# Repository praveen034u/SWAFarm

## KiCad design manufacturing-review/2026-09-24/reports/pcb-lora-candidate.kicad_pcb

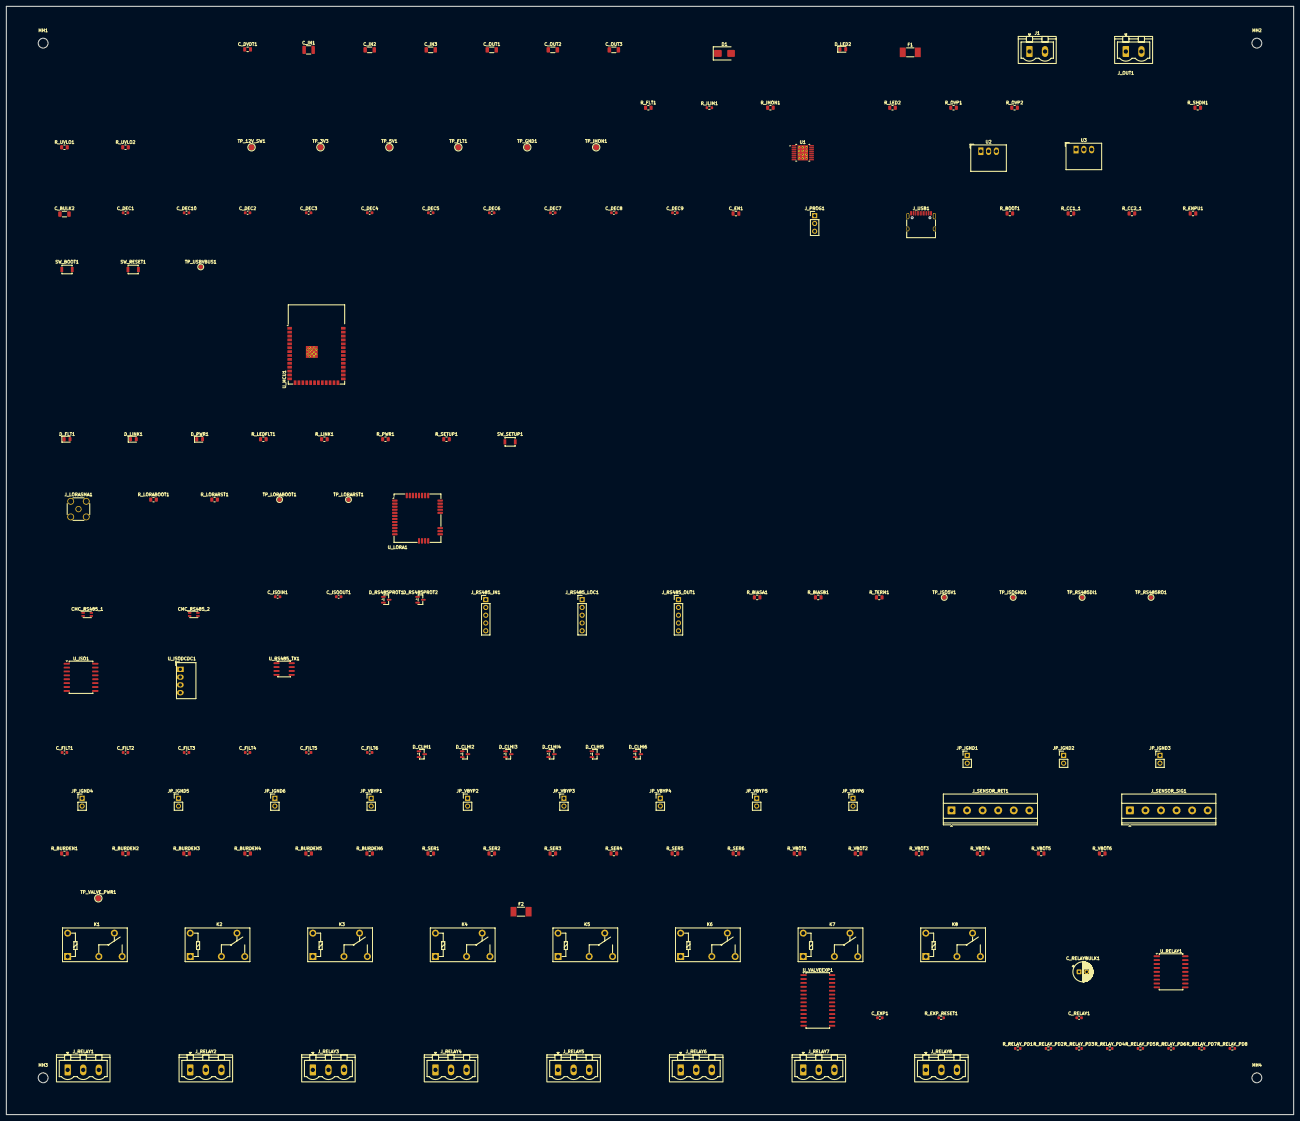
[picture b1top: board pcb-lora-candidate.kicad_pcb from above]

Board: 4 copper layers, 420.0 x 361.6 mm, 165 parts (0 on the bottom side), 114 nets, no tracks yet.

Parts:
CMC_RS485_1, CMC_RS485_2: 744232090; L_CommonMode_Wurth_WE-CNSW-1206
C_BULK2: 10uF; C_1206_3216Metric
C_DEC1, C_DEC2, C_DEC3, C_DEC4, C_DEC5, C_DEC6, C_DEC7, C_DEC8, C_DEC9, C_DEC10: 100nF; C_0603_1608Metric
C_DVDT1: 100nF 50V X7R; C_0805_2012Metric
C_EN1: 1uF; C_0805_2012Metric
C_EXP1: 100nF; C_0603_1608Metric
C_FILT1, C_FILT2, C_FILT3, C_FILT4, C_FILT5, C_FILT6: 100nF; C_0603_1608Metric
C_IN1: 10uF 63V X7R; C_1210_3225Metric
C_IN2, C_IN3: 10uF 25V; C_1206_3216Metric
C_ISOIN1: 100nF; C_0603_1608Metric
C_ISOOUT1: 100nF; C_0603_1608Metric
C_OUT1: 10uF 25V; C_1206_3216Metric
C_OUT2, C_OUT3: 22uF 10V; C_1206_3216Metric
C_RELAY1: 100nF; C_0603_1608Metric
C_RELAYBULK1: 100uF 25V; CP_Radial_D6.3mm_P2.50mm
D1: SMBJ18CA; D_SMB
D_CLHI1, D_CLHI2, D_CLHI3, D_CLHI4, D_CLHI5, D_CLHI6: BAV99; SOT-23
D_FLT1: Red; LED_0805_2012Metric
D_LED2: Green_3V3Present; LED_0805_2012Metric
D_LINK1: Yellow; LED_0805_2012Metric
D_PWR1: Green; LED_0805_2012Metric
D_RS485PROT1, D_RS485PROT2: SM712-02HTG; SOT-23
F1: 2A fast / 125V; Fuse_Littelfuse-NANO2-451_453
F2: 1A fast / 125V; Fuse_Littelfuse-NANO2-451_453
J1: 12V IN: + / GND; PhoenixContact_MSTBVA_2,5_2-G-5,08_1x02_P5.08mm_Vertical
JP_IGND1, JP_IGND2, JP_IGND3, JP_IGND4, JP_IGND5, JP_IGND6: I_mode_gnd; PinHeader_1x02_P2.54mm_Vertical
JP_VBYP1, JP_VBYP2, JP_VBYP3, JP_VBYP4, JP_VBYP5, JP_VBYP6: V_mode_bypass; PinHeader_1x02_P2.54mm_Vertical
J_LORASMA1: SMA_Bulkhead_Antenna; SMA_Amphenol_132134_Vertical
J_OUT1: AUX OUT: + / GND; PhoenixContact_MSTBVA_2,5_2-G-5,08_1x02_P5.08mm_Vertical
J_PROG1: Debug_UART_TX_RX_GND; PinHeader_1x03_P2.54mm_Vertical
J_RELAY1, J_RELAY2, J_RELAY3, J_RELAY4, J_RELAY5, J_RELAY6, J_RELAY7, J_RELAY8: COM / NO / NC; PhoenixContact_MSTBVA_2,5_3-G-5,08_1x03_P5.08mm_Vertical
J_RS485_IN1: M12_5P_A_Coded_RS485_Bus_In; PinHeader_1x05_P2.54mm_Vertical
J_RS485_LOC1: M12_5P_A_Coded_RS485_Local; PinHeader_1x05_P2.54mm_Vertical
J_RS485_OUT1: M12_5P_A_Coded_RS485_Bus_Out; PinHeader_1x05_P2.54mm_Vertical
J_SENSOR_RET1: SensorReturn_x6; TerminalBlock_Phoenix_MKDS-1,5-6-5.08_1x06_P5.08mm_Horizont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
J_SENSOR_SIG1: SensorSignal_x6; TerminalBlock_Phoenix_MKDS-1,5-6-5.08_1x06_P5.08mm_Horizont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
J_USB1: USB-C_Programming; USB_C_Receptacle_HRO_TYPE-C-31-M-12
K1, K2, K3, K4, K5, K6, K7, K8: G5Q-14 DC12; Relay_SPDT_Omron-G5Q-1
MH1, MH2, MH3, MH4: MountingHole_3.2mm_M3
R_BIASA1: 680; R_0805_2012Metric
R_BIASB1: 680; R_0805_2012Metric
R_BOOT1: 10k; R_0805_2012Metric
R_BURDEN1, R_BURDEN2, R_BURDEN3, R_BURDEN4, R_BURDEN5, R_BURDEN6: 150R; R_0805_2012Metric
R_CC1_1, R_CC2_1: 5.1k; R_0805_2012Metric
R_ENPU1: 10k; R_0805_2012Metric
R_EXP_RESET1: 10k; R_0603_1608Metric
R_FLT1: 10k; R_0805_2012Metric
R_ILIM1: 8.06k 1%; R_0603_1608Metric
R_IMON1: 10k; R_0805_2012Metric
R_LED2: 330; R_0805_2012Metric
R_LEDFLT1: 1k; R_0805_2012Metric
R_LINK1: 1k; R_0805_2012Metric
R_LORABOOT1: 10k; R_0805_2012Metric
R_LORARST1: 10k; R_0805_2012Metric
R_OVP1: 124k; R_0805_2012Metric
R_OVP2: 10k; R_0805_2012Metric
R_PWR1: 1k; R_0805_2012Metric
R_RELAY_PD1, R_RELAY_PD2, R_RELAY_PD3, R_RELAY_PD4, R_RELAY_PD5, R_RELAY_PD6, R_RELAY_PD7, R_RELAY_PD8: 47k; R_0603_1608Metric
R_SER1, R_SER2, R_SER3, R_SER4, R_SER5, R_SER6: 232k; R_0805_2012Metric
R_SETUP1: 10k; R_0805_2012Metric
R_SHDN1: 100k; R_0805_2012Metric
R_TERM1: 120R; R_0805_2012Metric
R_UVLO1: 64.9k; R_0805_2012Metric
R_UVLO2: 10k; R_0805_2012Metric
R_VBOT1, R_VBOT2, R_VBOT3, R_VBOT4, R_VBOT5, R_VBOT6: 100k; R_0805_2012Metric
SW_BOOT1: BOOT; SW_SPST_B3U-1000P
SW_RESET1: RESET; SW_SPST_B3U-1000P
SW_SETUP1: SETUP; SW_SPST_B3U-1000P
TP_3V3: +3V3; TestPoint_Pad_D2.0mm
TP_5V1: +5V; TestPoint_Pad_D2.0mm
TP_12V_SW1: 12V_SW; TestPoint_Pad_D2.0mm
TP_FLT1: EF_FLT_N; TestPoint_Pad_D2.0mm
TP_GND1: GND; TestPoint_Pad_D2.0mm
TP_IMON1: EF_IMON; TestPoint_Pad_D2.0mm
TP_ISO5V1: ISO_5V; TestPoint_Pad_D1.5mm
TP_ISOGND1: ISO_GND; TestPoint_Pad_D1.5mm
TP_LORABOOT1: LORA_BOOT0; TestPoint_Pad_D1.5mm
TP_LORARST1: LORA_RESET; TestPoint_Pad_D1.5mm
TP_RS485DI1: ISO_DI; TestPoint_Pad_D1.5mm
TP_RS485RO1: ISO_RO; TestPoint_Pad_D1.5mm
TP_USBVBUS1: USB_VBUS; TestPoint_Pad_D1.5mm
TP_VALVE_PWR1: +12V; TestPoint_Pad_D2.0mm
U1: TPS26600PWP; TPS26600PWP_Thermal_D0.30_P0.70
U2: R-78B5.0-2.0; Converter_DCDC_RECOM_R-78B-2.0_THT
U3: R-78B3.3-2.0; Converter_DCDC_RECOM_R-78B-2.0_THT
U_ISO1: ISO7761DW; SOIC-16W_7.5x10.3mm_P1.27mm
U_ISODCDC1: MEE1S0505SC; Converter_DCDC_Murata_MEE1SxxxxSC_THT
U_LORA1: RAK3172-T-8-SM-NI; RAK3172
U_MCU1: ESP32-S3-WROOM-1-N16R8; ESP32-S3-WROOM-1_Thermal_D0.30_P0.70
U_RELAY1: TBD62083AFWG,EL; SOIC-18W_7.5x11.6mm_P1.27mm
U_RS485_TX1: THVD1450DR; SOIC-8_3.9x4.9mm_P1.27mm
U_VALVEEXP1: MCP23S17-E/SO; SOIC-28W_7.5x17.9mm_P1.27mm

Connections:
12V_SW: C_IN2.1, C_IN3.1, C_OUT1.1, F2.1, J_OUT1.1, R_FLT1.1, TP_12V_SW1.1, U1.15, U1.16, U2.1, U3.1
+3V3: C_BULK2.1, C_DEC1.1, C_DEC2.1, C_DEC3.1, C_DEC4.1, C_DEC5.1, C_DEC6.1, C_DEC7.1, C_DEC8.1, C_DEC9.1, C_DEC10.1, C_EXP1.1, C_OUT3.1, D_CLHI1.2 (S), D_CLHI2.2 (S), D_CLHI3.2 (S), D_CLHI4.2 (S), D_CLHI5.2 (S), D_CLHI6.2 (S), D_LED2.2 (A), R_BOOT1.1, R_ENPU1.1, R_EXP_RESET1.1, R_LORARST1.1, R_SETUP1.1, TP_3V3.1, U3.3, U_ISO1.1 (Vcc1), U_LORA1.24 (VDD), U_MCU1.2, U_VALVEEXP1.9 (V_{DD})
+5V: C_ISOIN1.1, C_OUT2.1, TP_5V1.1, U2.3, U_ISODCDC1.2 (+Vin)
+12V: C_RELAY1.1, C_RELAYBULK1.1, F2.2, K1.5, K2.5, K3.5, K4.5, K5.5, K6.5, K7.5, K8.5, TP_VALVE_PWR1.1, U_RELAY1.10
/MCU/LED_FAULT: R_LEDFLT1.1, U_MCU1.33
/MCU/LED_LINK: R_LINK1.1, U_MCU1.32
/MCU/LED_PWR: R_PWR1.1, U_MCU1.31
/MCU/SETUP_BTN: R_SETUP1.2, SW_SETUP1.1, U_MCU1.22
/MCU/net_BOOT: R_BOOT1.2, SW_BOOT1.1, U_MCU1.27
/MCU/net_CHIP_EN: C_EN1.1, R_ENPU1.2, SW_RESET1.1, U_MCU1.3
/MCU/net_DEBUG_RX: J_PROG1.2, U_MCU1.36
/MCU/net_DEBUG_TX: J_PROG1.1, U_MCU1.37
/Motor Valve/COIL_LOW1: K1.1, U_RELAY1.18
/Motor Valve/COIL_LOW2: K2.1, U_RELAY1.17
/Motor Valve/COIL_LOW3: K3.1, U_RELAY1.16
/Motor Valve/COIL_LOW4: K4.1, U_RELAY1.15
/Motor Valve/COIL_LOW5: K5.1, U_RELAY1.14
/Motor Valve/COIL_LOW6: K6.1, U_RELAY1.13
/Motor Valve/COIL_LOW7: K7.1, U_RELAY1.12
/Motor Valve/COIL_LOW8: K8.1, U_RELAY1.11
/Motor Valve/EXP_RESET_N: R_EXP_RESET1.2, U_VALVEEXP1.18 (~RESET)
/Motor Valve/RELAY_CMD1: R_RELAY_PD1.1, U_RELAY1.1, U_VALVEEXP1.21 (GPA0)
/Motor Valve/RELAY_CMD2: R_RELAY_PD2.1, U_RELAY1.2, U_VALVEEXP1.22 (GPA1)
/Motor Valve/RELAY_CMD3: R_RELAY_PD3.1, U_RELAY1.3, U_VALVEEXP1.23 (GPA2)
/Motor Valve/RELAY_CMD4: R_RELAY_PD4.1, U_RELAY1.4, U_VALVEEXP1.24 (GPA3)
/Motor Valve/RELAY_CMD5: R_RELAY_PD5.1, U_RELAY1.5, U_VALVEEXP1.25 (GPA4)
/Motor Valve/RELAY_CMD6: R_RELAY_PD6.1, U_RELAY1.6, U_VALVEEXP1.26 (GPA5)
/Motor Valve/RELAY_CMD7: R_RELAY_PD7.1, U_RELAY1.7, U_VALVEEXP1.27 (GPA6)
/Motor Valve/RELAY_CMD8: R_RELAY_PD8.1, U_RELAY1.8, U_VALVEEXP1.28 (GPA7)
/Motor Valve/RLY1_COM: J_RELAY1.1, K1.2
/Motor Valve/RLY1_NC: J_RELAY1.3, K1.4
/Motor Valve/RLY1_NO: J_RELAY1.2, K1.3
/Motor Valve/RLY2_COM: J_RELAY2.1, K2.2
/Motor Valve/RLY2_NC: J_RELAY2.3, K2.4
/Motor Valve/RLY2_NO: J_RELAY2.2, K2.3
/Motor Valve/RLY3_COM: J_RELAY3.1, K3.2
/Motor Valve/RLY3_NC: J_RELAY3.3, K3.4
/Motor Valve/RLY3_NO: J_RELAY3.2, K3.3
/Motor Valve/RLY4_COM: J_RELAY4.1, K4.2
/Motor Valve/RLY4_NC: J_RELAY4.3, K4.4
/Motor Valve/RLY4_NO: J_RELAY4.2, K4.3
/Motor Valve/RLY5_COM: J_RELAY5.1, K5.2
/Motor Valve/RLY5_NC: J_RELAY5.3, K5.4
/Motor Valve/RLY5_NO: J_RELAY5.2, K5.3
/Motor Valve/RLY6_COM: J_RELAY6.1, K6.2
/Motor Valve/RLY6_NC: J_RELAY6.3, K6.4
/Motor Valve/RLY6_NO: J_RELAY6.2, K6.3
/Motor Valve/RLY7_COM: J_RELAY7.1, K7.2
/Motor Valve/RLY7_NC: J_RELAY7.3, K7.4
/Motor Valve/RLY7_NO: J_RELAY7.2, K7.3
/Motor Valve/RLY8_COM: J_RELAY8.1, K8.2
/Motor Valve/RLY8_NC: J_RELAY8.3, K8.4
/Motor Valve/RLY8_NO: J_RELAY8.2, K8.3
/Power/DC_IN_RAW_P: F1.1, J1.1
/Power/EF_DVDT: C_DVDT1.1, U1.12
/Power/EF_FLT_N: R_FLT1.2, TP_FLT1.1, U1.14
/Power/EF_ILIM: R_ILIM1.1, U1.11
/Power/EF_IMON: R_IMON1.1, TP_IMON1.1, U1.10
/Power/EF_OVP: R_OVP1.2, R_OVP2.1, U1.5
/Power/EF_RTN: C_DVDT1.2, R_ILIM1.2, R_IMON1.2, R_OVP2.2, R_UVLO2.2, U1.6, U1.8, U1.17
/Power/EF_SHDN: R_SHDN1.2, U1.7
/Power/EF_UVLO: R_UVLO1.2, R_UVLO2.1, U1.3
/Power/LED_3V3_K: D_LED2.1 (K), R_LED2.1
/Power/net_CC1: J_USB1.A5 (CC1), R_CC1_1.1
/Power/net_CC2: J_USB1.B5 (CC2), R_CC2_1.1
/Power/net_USB_VBUS: J_USB1.A4 (VBUS), J_USB1.A9 (VBUS), J_USB1.B4 (VBUS), J_USB1.B9 (VBUS), TP_USBVBUS1.1 (1_1)
/RS-485/net_IN_A_RAW: CMC_RS485_1.1, D_RS485PROT1.1 (A1), J_RS485_IN1.2
/RS-485/net_IN_B_RAW: CMC_RS485_1.4, D_RS485PROT1.2 (A2), J_RS485_IN1.3
/RS-485/net_ISO_DI: TP_RS485DI1.1 (1_1), U_ISO1.15 (OUTA), U_RS485_TX1.4 (DI)
/RS-485/net_ISO_DIR: U_ISO1.14 (OUTB), U_RS485_TX1.2 (~RE), U_RS485_TX1.3 (DE)
/RS-485/net_ISO_RO: TP_RS485RO1.1 (1_1), U_ISO1.10 (INF), U_RS485_TX1.1 (RO)
/RS-485/net_LOC_A_RAW: CMC_RS485_2.1, D_RS485PROT2.1 (A1), J_RS485_LOC1.2
/RS-485/net_LOC_B_RAW: CMC_RS485_2.4, D_RS485PROT2.2 (A2), J_RS485_LOC1.3
/RS-485/net_MAIN_A: CMC_RS485_1.2, CMC_RS485_2.2, J_RS485_OUT1.2, R_BIASA1.2, R_TERM1.1, U_RS485_TX1.6 (A)
/RS-485/net_MAIN_B: CMC_RS485_1.3, CMC_RS485_2.3, J_RS485_OUT1.3, R_BIASB1.1, R_TERM1.2, U_RS485_TX1.7 (B)
/Sensors & LORA/LORA_RF: J_LORASMA1.1 (In), U_LORA1.12 (RF)
/Sensors & LORA/net_CH1_SIG: JP_VBYP1.1, J_SENSOR_SIG1.1, R_SER1.1
/Sensors & LORA/net_CH2_SIG: JP_VBYP2.1, J_SENSOR_SIG1.2, R_SER2.1
/Sensors & LORA/net_CH3_SIG: JP_VBYP3.1, J_SENSOR_SIG1.3, R_SER3.1
/Sensors & LORA/net_CH4_SIG: JP_VBYP4.1, J_SENSOR_SIG1.4, R_SER4.1
/Sensors & LORA/net_CH5_SIG: JP_VBYP5.1, J_SENSOR_SIG1.5, R_SER5.1
/Sensors & LORA/net_CH6_SIG: JP_VBYP6.1, J_SENSOR_SIG1.6, R_SER6.1
/Sensors & LORA/net_LORA_BOOT0: R_LORABOOT1.1, TP_LORABOOT1.1 (1_1), U_LORA1.21 (BOOT0)
/Sensors & LORA/net_LORA_RST: R_LORARST1.2, TP_LORARST1.1 (1_1), U_LORA1.22 (~RST)
GND: C_BULK2.2, C_DEC1.2, C_DEC2.2, C_DEC3.2, C_DEC4.2, C_DEC5.2, C_DEC6.2, C_DEC7.2, C_DEC8.2, C_DEC9.2, C_DEC10.2, C_EN1.2, C_EXP1.2, C_FILT1.2, C_FILT2.2, C_FILT3.2, C_FILT4.2, C_FILT5.2, C_FILT6.2, C_IN1.2, C_IN2.2, C_IN3.2, C_ISOIN1.2, C_OUT1.2, C_OUT2.2, C_OUT3.2, C_RELAY1.2, C_RELAYBULK1.2, D1.2 (A2), D_CLHI1.1 (G), D_CLHI2.1 (G), D_CLHI3.1 (G), D_CLHI4.1 (G), D_CLHI5.1 (G), D_CLHI6.1 (G), D_FLT1.1 (K), D_LINK1.1 (K), D_PWR1.1 (K), J1.2, JP_IGND1.2, JP_IGND2.2, JP_IGND3.2, JP_IGND4.2, JP_IGND5.2, JP_IGND6.2, J_LORASMA1.2 (Ext), J_OUT1.2, J_PROG1.3, J_SENSOR_RET1.1, J_SENSOR_RET1.2, J_SENSOR_RET1.3, J_SENSOR_RET1.4, J_SENSOR_RET1.5, J_SENSOR_RET1.6, J_USB1.A1 (GND), J_USB1.A12 (GND), J_USB1.B1 (GND), J_USB1.B12 (GND), J_USB1.SH (SHIELD), R_CC1_1.2, R_CC2_1.2, R_LED2.2, R_LORABOOT1.2, R_RELAY_PD1.2, R_RELAY_PD2.2, R_RELAY_PD3.2, R_RELAY_PD4.2, R_RELAY_PD5.2, R_RELAY_PD6.2, R_RELAY_PD7.2, R_RELAY_PD8.2, R_VBOT1.2, R_VBOT2.2, R_VBOT3.2, R_VBOT4.2, R_VBOT5.2, R_VBOT6.2, SW_BOOT1.2, SW_RESET1.2, SW_SETUP1.2, TP_GND1.1, U1.9, U2.2, U3.2, U_ISO1.4 (INC), U_ISO1.5 (IND), U_ISO1.6 (INE), U_ISO1.8 (GND1), U_ISODCDC1.1 (-Vin), U_LORA1.11 (GND), U_LORA1.17 (GND), U_LORA1.18 (GND), U_LORA1.23 (GND), U_LORA1.28 (GND), U_MCU1.1, U_MCU1.40, U_MCU1.41, U_RELAY1.9, U_VALVEEXP1.10 (V_{SS}), U_VALVEEXP1.15 (A0), U_VALVEEXP1.16 (A1), U_VALVEEXP1.17 (A2)
ISO_5V: C_ISOOUT1.1, R_BIASA1.1, TP_ISO5V1.1 (1_1), U_ISO1.16 (Vcc2), U_ISODCDC1.4 (+Vout), U_RS485_TX1.8 (VCC)
ISO_GND: C_ISOOUT1.2, D_RS485PROT1.3 (common), D_RS485PROT2.3 (common), J_RS485_IN1.1, J_RS485_IN1.5, J_RS485_LOC1.1, J_RS485_LOC1.5, J_RS485_OUT1.1, J_RS485_OUT1.5, R_BIASB1.2, TP_ISOGND1.1 (1_1), U_ISO1.9 (GND2), U_ISODCDC1.3 (-Vout), U_RS485_TX1.5 (GND)
LORA_UART_RX: U_LORA1.2 (UART2_TX/PA2), U_MCU1.11
LORA_UART_TX: U_LORA1.1 (UART2_RX/PA3), U_MCU1.10
unnamed: D_FLT1.2 (A), R_LEDFLT1.2
unnamed: D_LINK1.2 (A), R_LINK1.2
unnamed: D_PWR1.2 (A), R_PWR1.2
unnamed: JP_IGND1.1, R_BURDEN1.2
unnamed: JP_IGND2.1, R_BURDEN2.2
unnamed: JP_IGND3.1, R_BURDEN3.2
unnamed: JP_IGND4.1, R_BURDEN4.2
unnamed: JP_IGND5.1, R_BURDEN5.2
unnamed: JP_IGND6.1, R_BURDEN6.2
RS485_DE: U_ISO1.3 (INB), U_MCU1.34
RS485_RX: U_ISO1.7 (OUTF), U_MCU1.9
RS485_TX: U_ISO1.2 (INA), U_MCU1.8
SENSOR_CH1: C_FILT1.1, D_CLHI1.3 (D), JP_VBYP1.2, R_BURDEN1.1, R_SER1.2, R_VBOT1.1, U_MCU1.39
SENSOR_CH2: C_FILT2.1, D_CLHI2.3 (D), JP_VBYP2.2, R_BURDEN2.1, R_SER2.2, R_VBOT2.1, U_MCU1.38
SENSOR_CH3: C_FILT3.1, D_CLHI3.3 (D), JP_VBYP3.2, R_BURDEN3.1, R_SER3.2, R_VBOT3.1, U_MCU1.4
SENSOR_CH4: C_FILT4.1, D_CLHI4.3 (D), JP_VBYP4.2, R_BURDEN4.1, R_SER4.2, R_VBOT4.1, U_MCU1.5
SENSOR_CH5: C_FILT5.1, D_CLHI5.3 (D), JP_VBYP5.2, R_BURDEN5.1, R_SER5.2, R_VBOT5.1, U_MCU1.6
SENSOR_CH6: C_FILT6.1, D_CLHI6.3 (D), JP_VBYP6.2, R_BURDEN6.1, R_SER6.2, R_VBOT6.1, U_MCU1.7
VALVE_SPI_CS: U_MCU1.18, U_VALVEEXP1.11 (~CS)
VALVE_SPI_MISO: U_MCU1.21, U_VALVEEXP1.14 (SO)
VALVE_SPI_MOSI: U_MCU1.19, U_VALVEEXP1.13 (SI)
VALVE_SPI_SCLK: U_MCU1.20, U_VALVEEXP1.12 (SCK)
VIN_12V: C_IN1.1, D1.1 (A1), F1.2, R_OVP1.1, R_SHDN1.1, R_UVLO1.1, U1.1, U1.2
net_USB_DM: J_USB1.A7 (D-), J_USB1.B7 (D-), U_MCU1.13
net_USB_DP: J_USB1.A6 (D+), J_USB1.B6 (D+), U_MCU1.14
